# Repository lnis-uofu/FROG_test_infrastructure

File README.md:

OpenFPGA-FROG_12nm-Infrastructure is the repository containing all the informations regarding LNIS's FROG12nm based boards.
Here is a description of this repository content, more detailled Readmes to be found inside each directory.

# Pre-requisites

Operating system:

There is no operating system hard requirement, however development has been done under <complete OS> hence we recommend using this one especially when working on the firmware.

Development tools:

- Eagle 9.6.2 - Download [HERE](http://eagle.autodesk.com/eagle/software-versions/50)
- AutoCAD 2022 (optional, Drawing tool for wirebonding schematics)  - Download [HERE](https://www.autodesk.com/products/autocad/free-trial)
- Vivado 2020 - Download [HERE](https://www.xilinx.com/support/download/index.html/content/xilinx/en/downloadNav/vivado-design-tools/2020-3.html)

# Directory description

 - ./Packaging: Package manufacturing & assembly files with documentation. We employed the Open Source BaseJump UCSD_BGA_332 from the Bespoke Silicon Group (https://bsg.ai).
 - ./Testboard: Contains design files for every board / component related to the POSHtestbed project. Also contains testfirmware that has been used to test FROG chip.
 - ./Demoboard: Design files for the 3 demoboard versions.

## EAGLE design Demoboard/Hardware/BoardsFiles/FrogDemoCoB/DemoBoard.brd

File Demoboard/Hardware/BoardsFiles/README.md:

#BoardsFiles Folder Structure

TODO: Describe the 3 boards and what's inside the folders

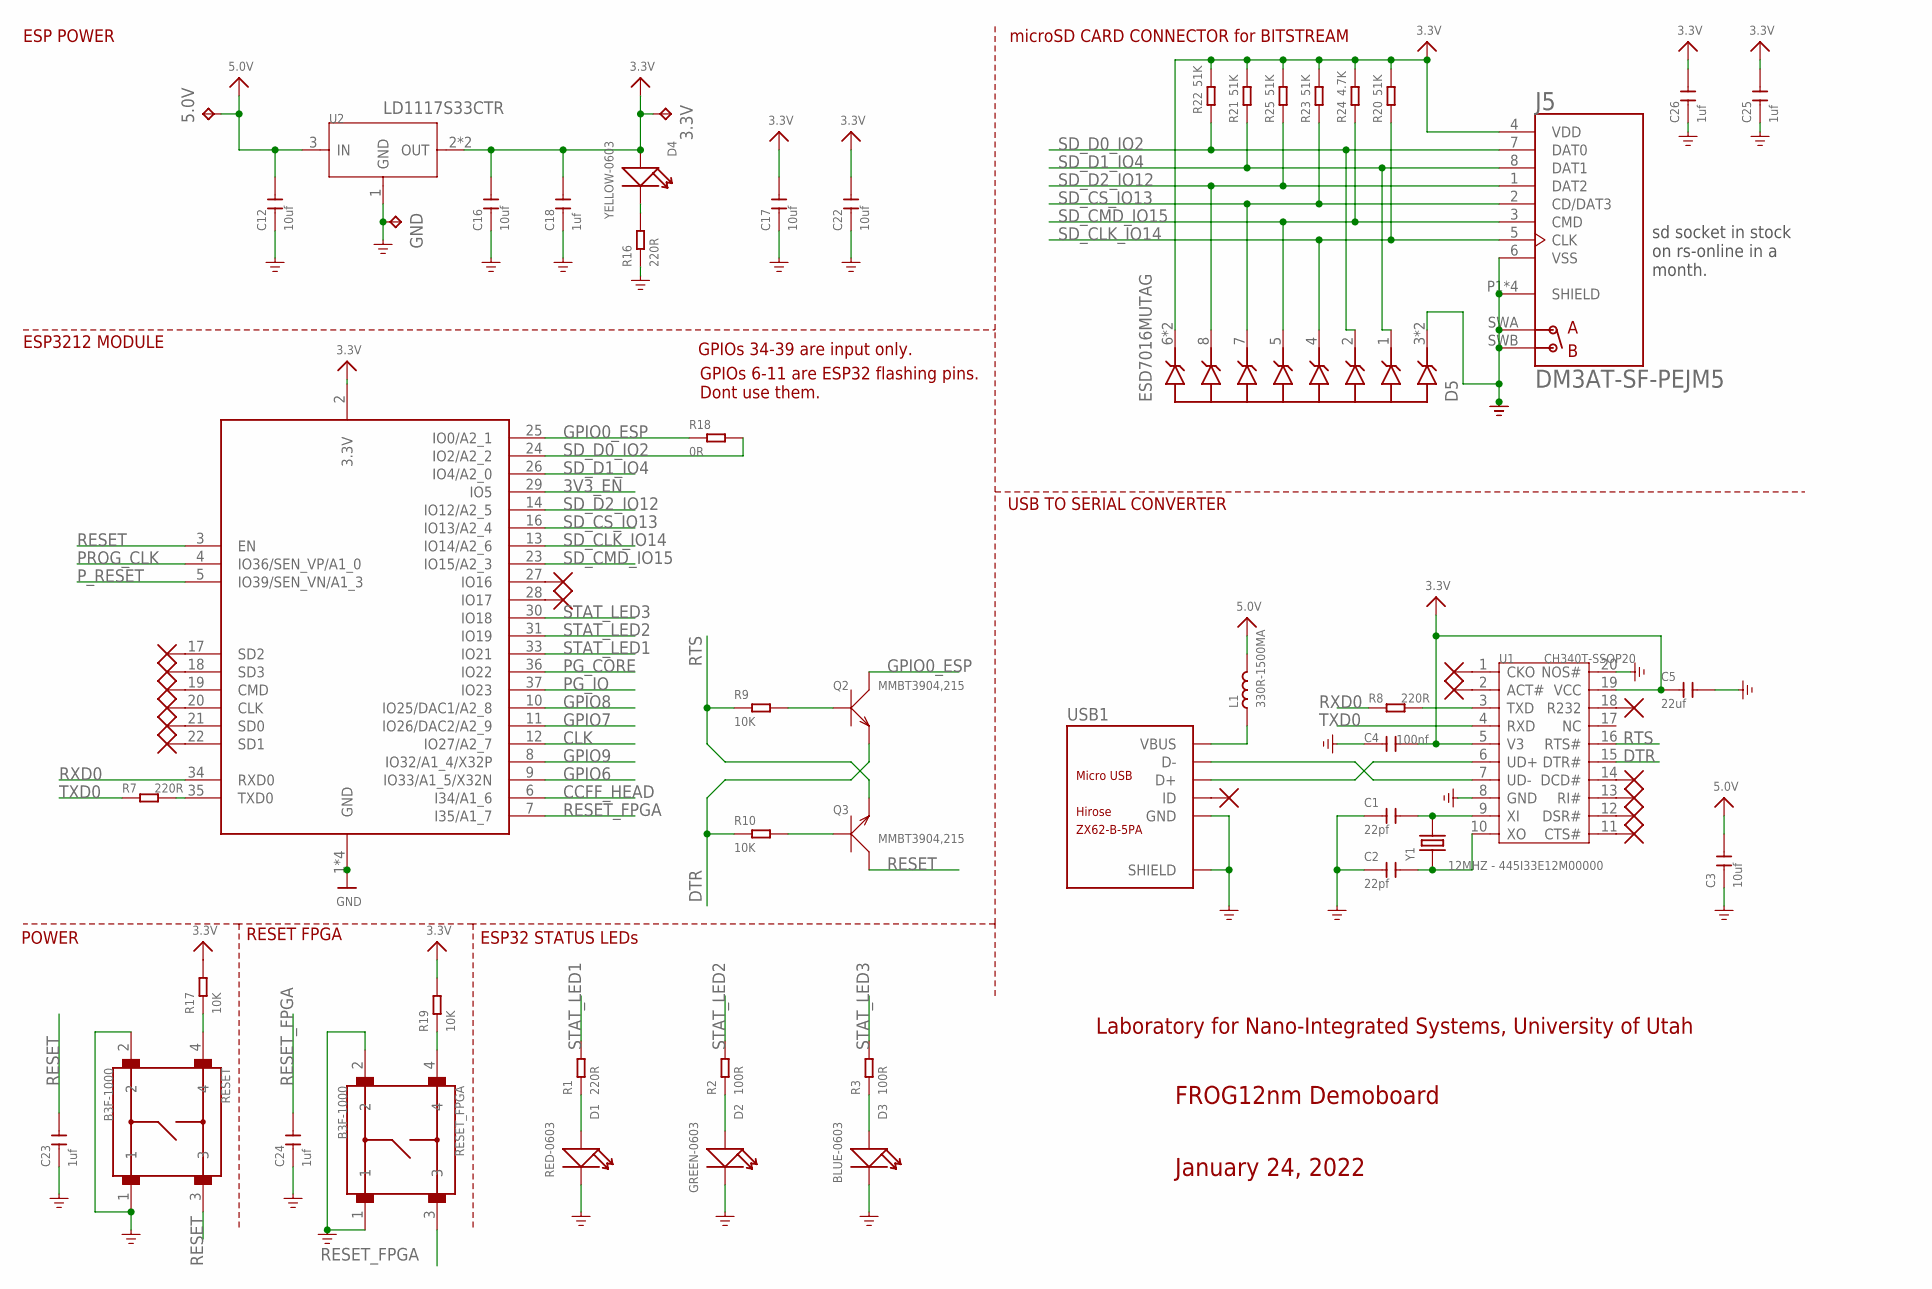
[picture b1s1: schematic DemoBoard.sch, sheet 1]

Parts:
3.3V, 5.0V: TPTP20SQ; TP20SQ
C1, C2: 22pf; C0603
C3, C12, C16, C17, C22: 10uf; C0603
C4: 100nf; C0603
C5: 22uf; C0805
C18, C23, C24, C25, C26: 1uf; C0603
D1: RED-0603; LED-0603
D2: GREEN-0603; LED-0603
D3: BLUE-0603; LED-0603
D4: YELLOW-0603; LED-0603
D5: ESD7016MUTAG; TVS_ESD7016MUTAG
GND: TPTP20SQ; TP20SQ
J5: DM3AT-SF-PEJM5; HRS_DM3AT-SF-PEJM5
L1: 330R-1500MA; L0805
Q2, Q3: MMBT3904,215; SOT-23
R1, R7, R8, R16: 220R; R0603
R2, R3: 100R; R0603
R9, R10, R17, R19: 10K; R0603
R18: 0R; R0603
R20, R21, R22, R23, R25: 51K; R0603
R24: 4.7K; R0603
RESET: B3F-1000; SW_B3F-1000
RESET_FPGA: B3F-1000; SW_B3F-1000
U1: CH340T-SSOP20; SSOP20-0.65-7.6X5.2MM
U2: PMIC-CJT1117-3.3(SOT223); SOT-223; MPN LD1117S33CTR
U3: ESP32_WROOM32_SKINNY; WROOM32_SKINNY
USB1: ZX62-B-5PA; MICRO-USB5+6P-SMD-0.65-AB
Y1: 12MHZ - 445I33E12M00000; X2-SMD-5.0X3.2X1.3MM

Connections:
3.3V: 3.3V.TP, C4.2, C5.1, C16.2, C17.2, C18.2, C22.2, C25.2, C26.2, D4.+, D5.6 (GND), D5.9 (GND), J5.4 (VDD), R17.2, R19.2, R20.2, R21.2, R22.2, R23.2, R24.2, R25.2, U1.5 (V3), U1.19 (VCC), U2.2 (OUT), U2.TER (OUT), U3.2 (3.3V); also elsewhere on the board
3V3_EN: U3.29 (IO5); also elsewhere on the board
5.0V: 5.0V.TP, C3.2, C12.2, L1.2, U2.3 (IN); also elsewhere on the board
CCFF_HEAD: U3.6 (I34/A1_6); also elsewhere on the board
CLK: U3.12 (IO27/A2_7); also elsewhere on the board
DTR: Q2.2 (E), R10.1, U1.15 (DTR#)
GND: C1.1, C2.1, C3.1, C4.1, C5.2, C12.1, C16.1, C17.1, C18.1, C22.1, C23.1, C24.1, C25.1, C26.1, D1.-, D2.-, D3.-, D5.3 (VBUS), D5.10 (VBUS), GND.TP, J5.6 (VSS), J5.P1 (SHIELD), J5.P2 (SHIELD), J5.P3 (SHIELD), J5.P4 (SHIELD), J5.SWA (A), J5.SWB (B), R16.1, RESET.1, RESET.2, RESET_FPGA.1, RESET_FPGA.2, U1.8 (GND), U1.20 (NOS#), U2.1 (GND), U3.1 (GND), U3.15 (GND), U3.38 (GND), U3.P$1 (GND), USB1.5 (GND), USB1.P1 (SHIELD), USB1.P2 (SHIELD), USB1.P3_1 (SHIELD), USB1.P3_2 (SHIELD), USB1.P3_3 (SHIELD), USB1.P4_1 (SHIELD), USB1.P4_2 (SHIELD), USB1.P4_3 (SHIELD), USB1.P5 (SHIELD), USB1.P6 (SHIELD); also elsewhere on the board
GPIO0_ESP: Q2.3 (C), R18.1, U3.25 (IO0/A2_1)
GPIO6: U3.9 (IO33/A1_5/X32N); also elsewhere on the board
GPIO7: U3.11 (IO26/DAC2/A2_9); also elsewhere on the board
GPIO8: U3.10 (IO25/DAC1/A2_8); also elsewhere on the board
GPIO9: U3.8 (IO32/A1_4/X32P); also elsewhere on the board
unnamed: D2.+, R2.1
unnamed: R17.1, RESET.4
unnamed: R19.1, RESET_FPGA.4
unnamed: D1.+, R1.1
unnamed: Q3.1 (B), R10.2
unnamed: Q2.1 (B), R9.2
unnamed: D3.+, R3.1
unnamed: D4.-, R16.2
unnamed: U1.7 (UD-), USB1.2 (D-)
unnamed: U1.6 (UD+), USB1.3 (D+)
unnamed: C1.2, U1.9 (XI), Y1.2
unnamed: C2.2, U1.10 (XO), Y1.1
unnamed: R8.2, U1.3 (TXD)
unnamed: R7.2, U3.35 (TXD0)
PG_CORE: U3.36 (IO22); also elsewhere on the board
PG_IO: U3.37 (IO23); also elsewhere on the board
PROG_CLK: U3.4 (IO36/SEN_VP/A1_0); also elsewhere on the board
P_RESET: U3.5 (IO39/SEN_VN/A1_3); also elsewhere on the board
RESET: C23.2, Q3.3 (C), RESET.3, U3.3 (EN)
RESET_FPGA: C24.2, RESET_FPGA.3, U3.7 (I35/A1_7); also elsewhere on the board
RTS: Q3.2 (E), R9.1, U1.16 (RTS#)
RXD0: R8.1, U3.34 (RXD0)
SD_CLK_IO14: D5.4 (I/O3), J5.5 (CLK), R20.1, U3.13 (IO14/A2_6)
SD_CMD_IO15: D5.5 (I/O4), J5.3 (CMD), R24.1, U3.23 (IO15/A2_3)
SD_CS_IO13: D5.7 (I/O5), J5.2 (CD/DAT3), R23.1, U3.16 (IO13/A2_4)
SD_D0_IO2: D5.2 (I/O2), J5.7 (DAT0), R18.2, R22.1, U3.24 (IO2/A2_2)
SD_D1_IO4: D5.1 (I/O1), J5.8 (DAT1), R21.1, U3.26 (IO4/A2_0)
SD_D2_IO12: D5.8 (I/O6), J5.1 (DAT2), R25.1, U3.14 (IO12/A2_5)
STAT_LED1: R1.2, U3.33 (IO21)
STAT_LED2: R2.2, U3.31 (IO19)
STAT_LED3: R3.2, U3.30 (IO18)
TXD0: R7.1, U1.4 (RXD)
VBUS: L1.1, USB1.1 (VBUS)

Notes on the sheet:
ESP POWER
RESET FPGA
USB TO SERIAL CONVERTER
ESP3212 MODULE
POWER
microSD CARD CONNECTOR for BITSTREAM
FROG12nm Demoboard
January 24, 2022
ESP32 STATUS LEDs
GPIOs 34-39 are input only.
Laboratory for Nano-Integrated Systems, University of Utah
GPIOs 6-11 are ESP32 flashing pins. Dont use them.
sd socket in stock on rs-online in a month.

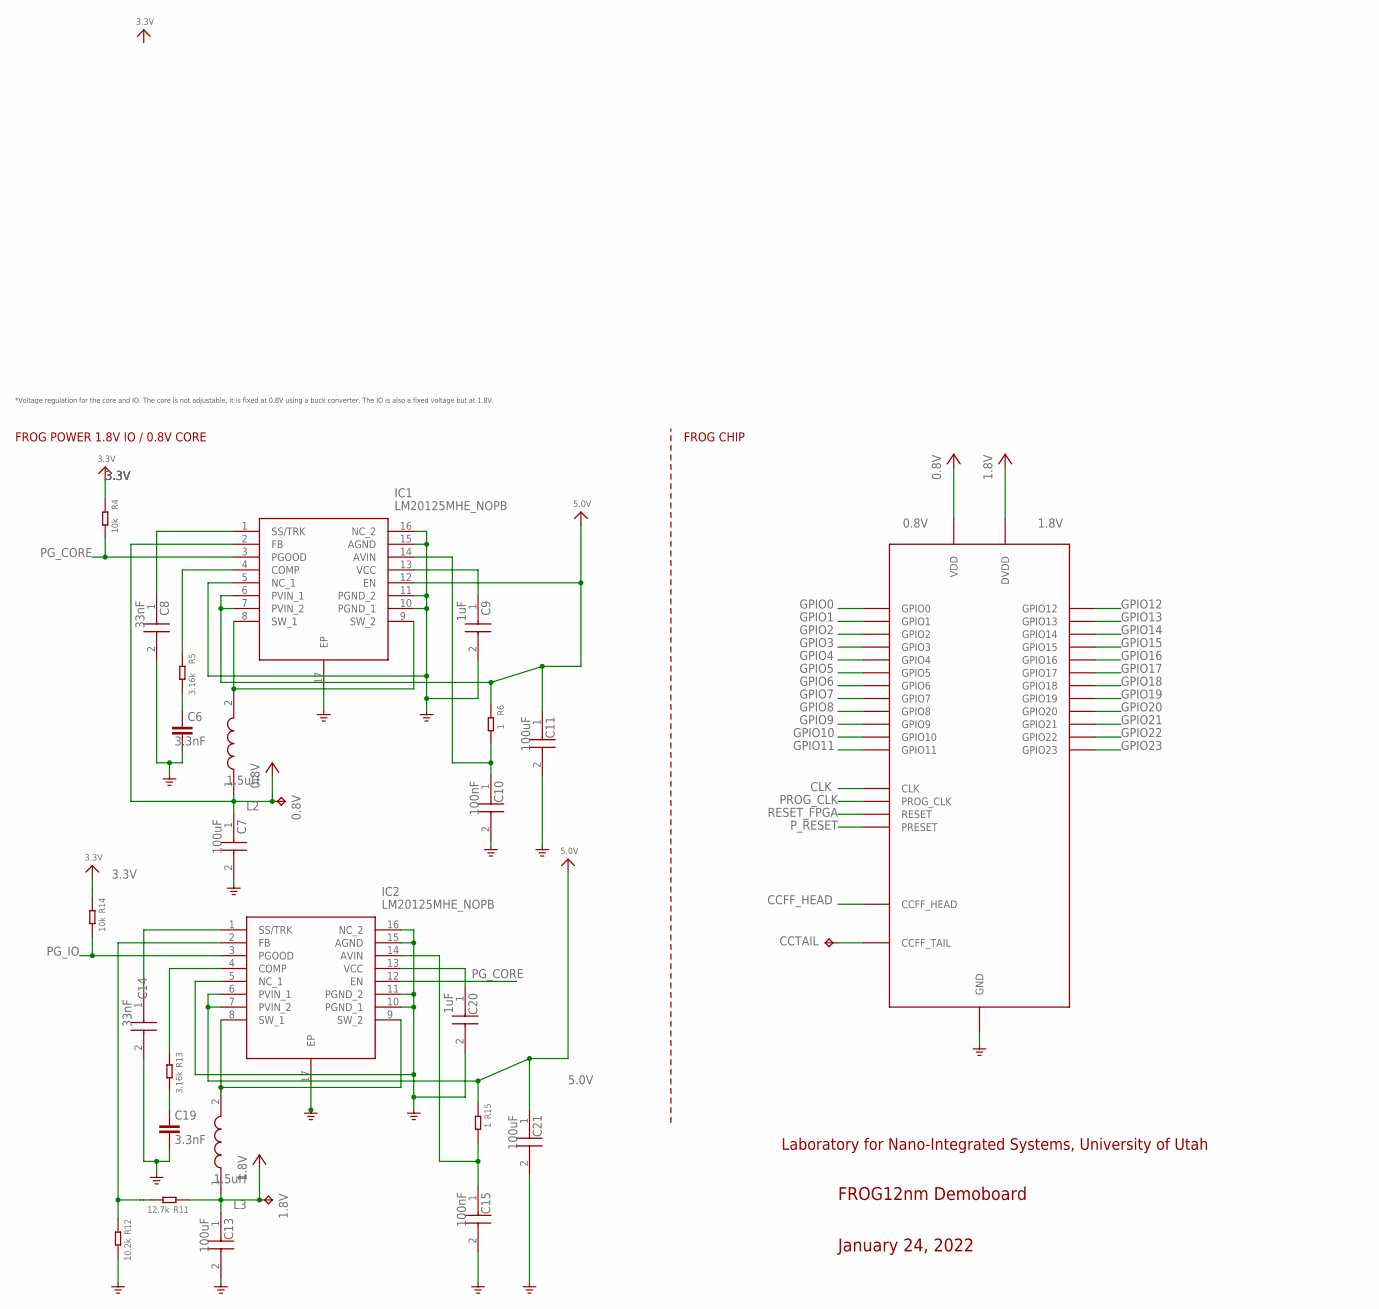
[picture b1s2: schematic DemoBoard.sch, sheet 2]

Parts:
0.8V, 1.8V: TPTP20SQ; TP20SQ
C6, C19: 3.3nF; CAPC1608X85
C7, C11, C13, C21: 100uF; CAPC3225X270N
C8, C14: 33nF; CAPC1608X97N
C9, C20: 1uF; CAPC1005X55N
C10, C15: 100nF; CAPC1005X55N
CCTAIL: TPPAD1-13; P1-13
IC1, IC2: LM20125MHE_NOPB; SOP65P640X120-17N
L2, L3: 1.5uH; INDPM7066X300N
R4, R14: 10k; R0603
R5, R13: 3.16k; R0603
R6, R15: 1; R0603
R11: 12.7k; R0603
R12: 10.2k; R0603
U5: FROG12NMCOBCOB; FROG_COB

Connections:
0.8V: 0.8V.TP, C7.1, IC1.2 (FB), L2.1, U5.VDD_CORE (VDD)
1.8V: 1.8V.TP, C13.1, L3.1, R11.1, U5.VDD_IO (DVDD)
3.3V: R4.1, R14.1; also elsewhere on the board
5.0V: C11.1, C21.1, IC1.6 (PVIN_1), IC1.7 (PVIN_2), IC1.12 (EN), IC2.6 (PVIN_1), IC2.7 (PVIN_2), R6.1, R15.1; also elsewhere on the board
CCFF_HEAD: U5.CCFFHEAD (CCFF_HEAD); also elsewhere on the board
CLK: U5.CLK; also elsewhere on the board
GND: C6.2, C7.2, C8.2, C9.2, C10.2, C11.2, C13.2, C14.2, C15.2, C19.2, C20.2, C21.2, IC1.5 (NC_1), IC1.10 (PGND_1), IC1.11 (PGND_2), IC1.15 (AGND), IC1.16 (NC_2), IC1.17 (EP), IC2.5 (NC_1), IC2.10 (PGND_1), IC2.11 (PGND_2), IC2.15 (AGND), IC2.16 (NC_2), IC2.17 (EP), R12.2, U5.GND; also elsewhere on the board
GPIO0: U5.GPIO0; also elsewhere on the board
GPIO1: U5.GPIO1; also elsewhere on the board
GPIO2: U5.GPIO2; also elsewhere on the board
GPIO3: U5.GPIO3; also elsewhere on the board
GPIO4: U5.GPIO4; also elsewhere on the board
GPIO5: U5.GPIO5; also elsewhere on the board
GPIO6: U5.GPIO6; also elsewhere on the board
GPIO7: U5.GPIO7; also elsewhere on the board
GPIO8: U5.GPIO8; also elsewhere on the board
GPIO9: U5.GPIO9; also elsewhere on the board
GPIO10: U5.GPIO10; also elsewhere on the board
GPIO11: U5.GPIO11; also elsewhere on the board
GPIO12: U5.GPIO12; also elsewhere on the board
GPIO13: U5.GPIO13; also elsewhere on the board
GPIO14: U5.GPIO14; also elsewhere on the board
GPIO15: U5.GPIO15; also elsewhere on the board
GPIO16: U5.GPIO16; also elsewhere on the board
GPIO17: U5.GPIO17; also elsewhere on the board
GPIO18: U5.GPIO18; also elsewhere on the board
GPIO19: U5.GPIO19; also elsewhere on the board
GPIO20: U5.GPIO20; also elsewhere on the board
GPIO21: U5.GPIO21; also elsewhere on the board
GPIO22: U5.GPIO22; also elsewhere on the board
GPIO23: U5.GPIO23; also elsewhere on the board
unnamed: IC1.4 (COMP), R5.1
unnamed: C6.1, R5.2
unnamed: C9.1, IC1.13 (VCC)
unnamed: C8.1, IC1.1 (SS/TRK)
unnamed: IC1.8 (SW_1), IC1.9 (SW_2), L2.2
unnamed: CCTAIL.TP, U5.CCFFTAIL (CCFF_TAIL)
unnamed: C10.1, IC1.14 (AVIN), R6.2
unnamed: IC2.4 (COMP), R13.1
unnamed: C19.1, R13.2
unnamed: C20.1, IC2.13 (VCC)
unnamed: C14.1, IC2.1 (SS/TRK)
unnamed: IC2.8 (SW_1), IC2.9 (SW_2), L3.2
unnamed: C15.1, IC2.14 (AVIN), R15.2
PG_CORE: IC1.3 (PGOOD), IC2.12 (EN), R4.2; also elsewhere on the board
PG_IO: IC2.3 (PGOOD), R14.2; also elsewhere on the board
PROG_CLK: U5.PROGCLK (PROG_CLK); also elsewhere on the board
P_RESET: U5.PRESET; also elsewhere on the board
RESET_FPGA: U5.RESET; also elsewhere on the board
VDD_CORE: IC2.2 (FB), R11.2, R12.1

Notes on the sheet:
FROG12nm Demoboard
January 24, 2022
Laboratory for Nano-Integrated Systems, University of Utah
*Voltage regulation for the core and IO. The core is not adjustable, it is fixed at 0.8V using a buck converter. The IO is also a fixed voltage but at 1.8V.
FROG POWER 1.8V IO / 0.8V CORE
FROG CHIP

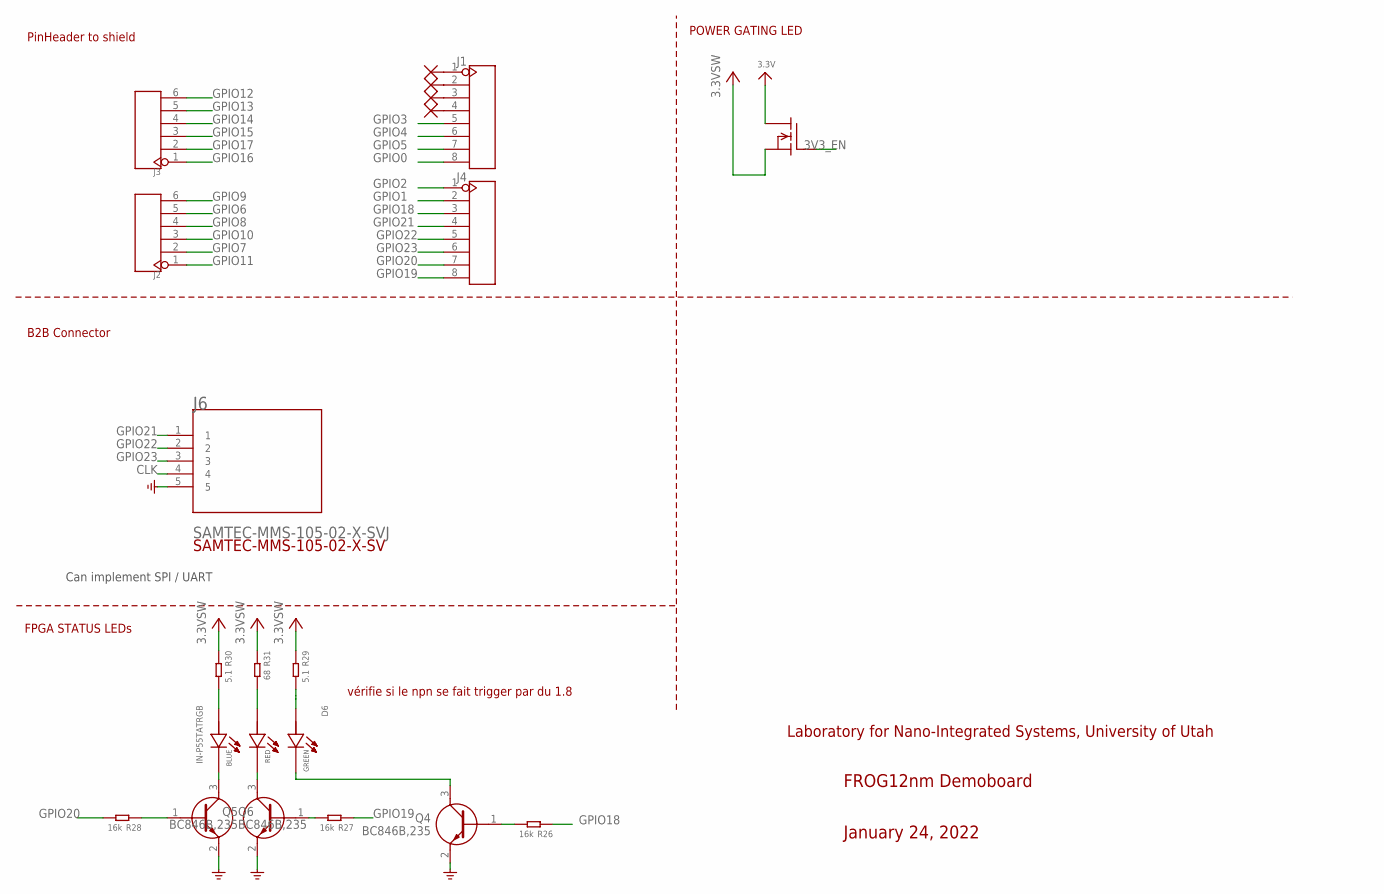
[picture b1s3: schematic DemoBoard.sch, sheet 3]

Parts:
D6: IN-P55TATRGB; LED_IN-P55TATRGB
J1, J4: HEADER-8P-2.54; 8P-2.54
J2, J3: HEADER-6P-55/35MIL; 6P-2.54-55/35MIL
J6: SAMTEC-MMS-105-02-X-SVJ; SAMTEC-MMS-105-02-X-SV
Q1: IRLML0030TRPBF; SOT23
Q4, Q5, Q6: BC846B,235; SOT95P230X110-3N
R26, R27, R28: 16k; R0603
R29, R30: 5.1; R0603
R31: 68; R0603

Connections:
3.3V: Q1.3 (D); also elsewhere on the board
3.3VSW: Q1.2 (S), R29.1, R30.1, R31.1
3V3_EN: Q1.1 (G); also elsewhere on the board
CLK: J6.4; also elsewhere on the board
GND: J6.5, Q4.2 (E), Q5.2 (E), Q6.2 (E); also elsewhere on the board
GPIO0: J1.8; also elsewhere on the board
GPIO1: J4.2; also elsewhere on the board
GPIO2: J4.1; also elsewhere on the board
GPIO3: J1.5; also elsewhere on the board
GPIO4: J1.6; also elsewhere on the board
GPIO5: J1.7; also elsewhere on the board
GPIO6: J2.5; also elsewhere on the board
GPIO7: J2.2; also elsewhere on the board
GPIO8: J2.4; also elsewhere on the board
GPIO9: J2.6; also elsewhere on the board
GPIO10: J2.3; also elsewhere on the board
GPIO11: J2.1; also elsewhere on the board
GPIO12: J3.6; also elsewhere on the board
GPIO13: J3.5; also elsewhere on the board
GPIO14: J3.4; also elsewhere on the board
GPIO15: J3.3; also elsewhere on the board
GPIO16: J3.1; also elsewhere on the board
GPIO17: J3.2; also elsewhere on the board
GPIO18: J4.3, R26.1; also elsewhere on the board
GPIO19: J4.8, R27.1; also elsewhere on the board
GPIO20: J4.7, R28.2; also elsewhere on the board
GPIO21: J4.4, J6.1; also elsewhere on the board
GPIO22: J4.5, J6.2; also elsewhere on the board
GPIO23: J4.6, J6.3; also elsewhere on the board
unnamed: D6.1 (B_C), Q6.3 (C)
unnamed: Q5.1 (B), R27.2
unnamed: D6.2 (R_C), Q5.3 (C)
unnamed: D6.3 (G_C), Q4.3 (C)
unnamed: Q6.1 (B), R28.1
unnamed: Q4.1 (B), R26.2
unnamed: D6.5 (R_A), R31.2
VCC2: D6.4 (G_A), D6.6 (B_A), R29.2, R30.2

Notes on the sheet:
FROG12nm Demoboard
January 24, 2022
Laboratory for Nano-Integrated Systems, University of Utah
B2B Connector
Can implement SPI / UART
PinHeader to shield
FPGA STATUS LEDs
vérifie si le npn se fait trigger par du 1.8
POWER GATING LED

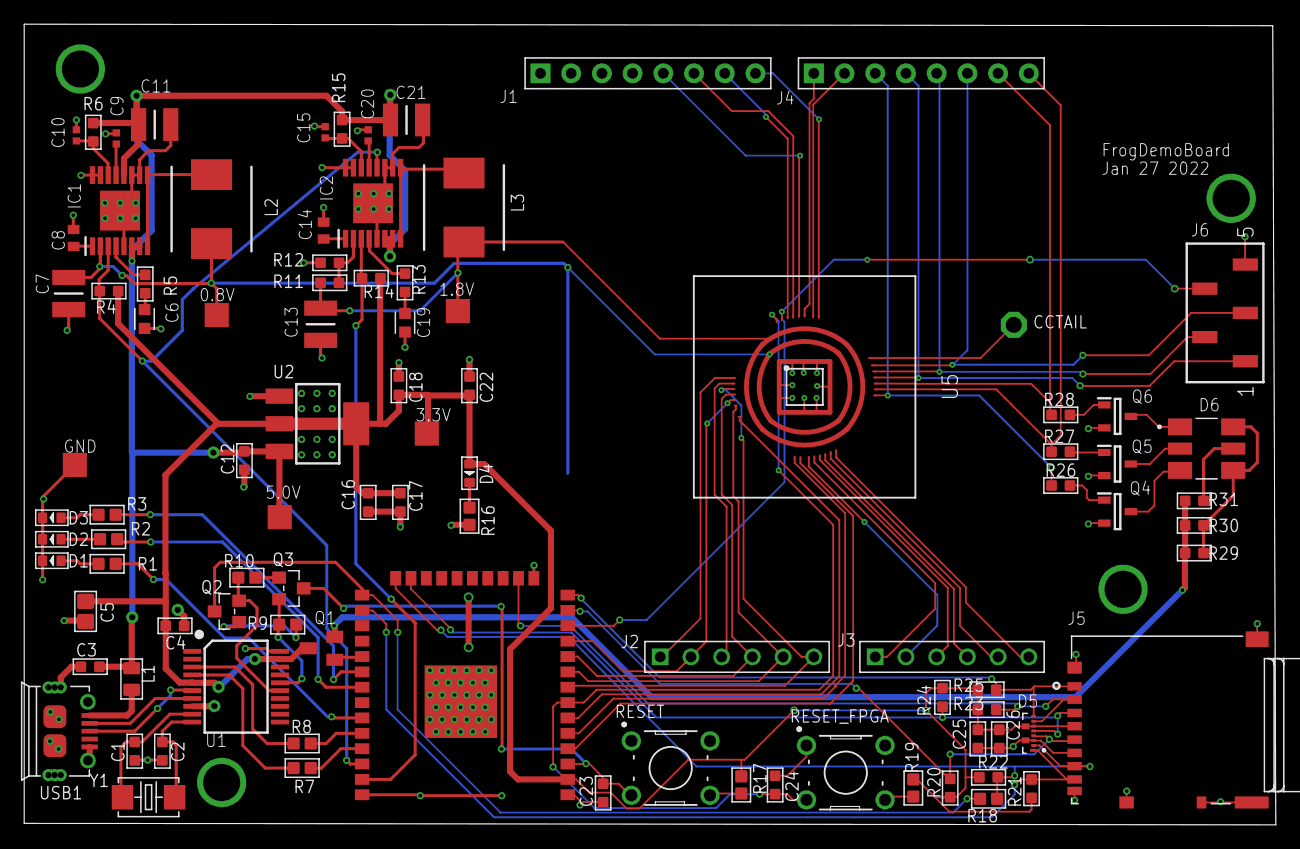
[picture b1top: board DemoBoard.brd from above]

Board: 2 copper layers, 103.5 x 66.2 mm, 94 parts (0 on the bottom side), 90 nets.

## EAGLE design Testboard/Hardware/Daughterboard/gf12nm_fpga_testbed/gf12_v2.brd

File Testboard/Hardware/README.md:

The testboard hardware folder contains design and documentation files for the POSH project test bed,
baseboard for the Trenz Electronic UltraSOM+ MPSoC (TE0803) and an additional custom daughter board (TEBF0808) to connect a VLSI circuit to be tested.

# Directory description

- ./AP-TEBF0808-04: Baseboard design files for the POSHtestbed project.
- ./Daughterboard: Custom board to connect FROG12_nm chip to the baseboard.
- ./ULTRASoMCarier: Carier card for above listed boards.
- ./Libraries: Common libraries for the project.
- ./Documentation: Boards documentation as well as critical components datasheets.
- ./TestSocket: TestSocket documentation that's being used to plug chips for testing.

# Trenz sources

UltraSOM MPSoC:
https://shop.trenz-electronic.de/en/TE0803-03-4BE11-A-MPSoC-Module-with-Xilinx-Zynq-UltraScale-ZU4EG-1E-2-GByte-DDR4-5.2-x-7.6-cm

Carrier Card:
https://shop.trenz-electronic.de/en/TEBF0808-04A-UltraITX-Baseboard-for-Trenz-Electronic-TE080X-UltraSOM

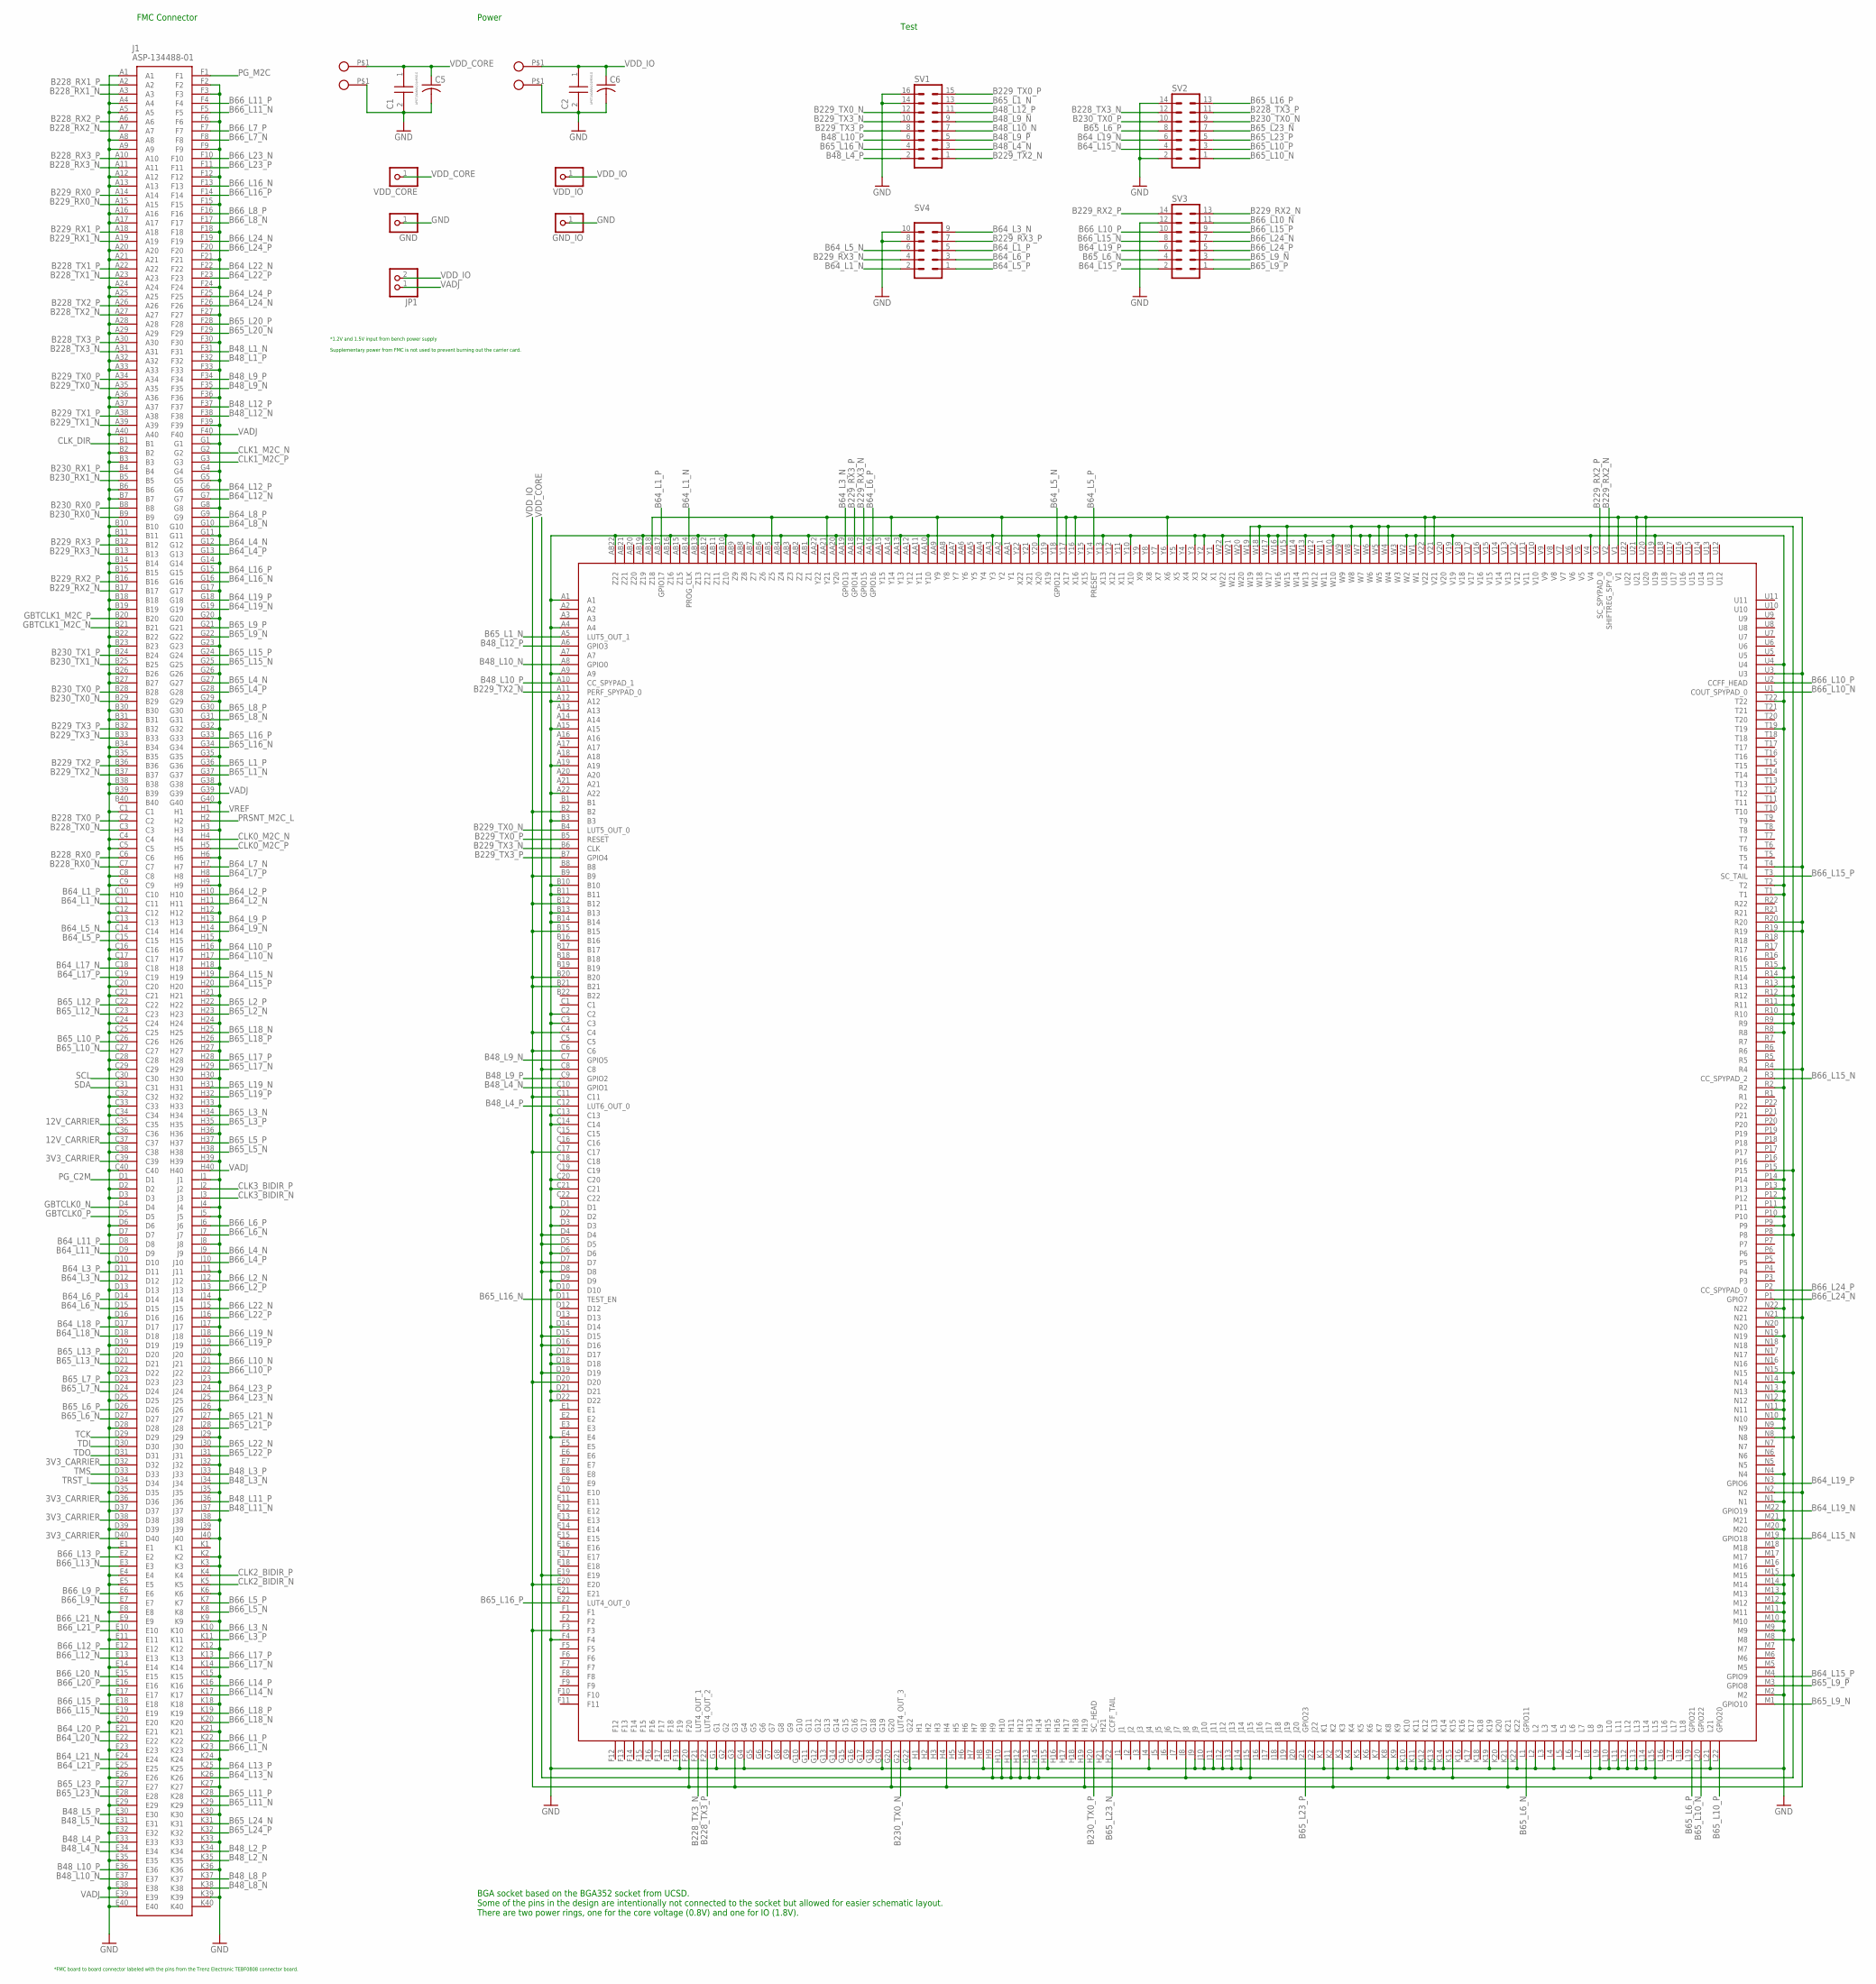
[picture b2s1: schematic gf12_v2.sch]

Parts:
C1, C2: APXT160ARA101ME61G; CAPAE530X610N
C5, C6: C-USC0805K; C0805K
GND: PINHD-1X1; 1X01
GND_IO: PINHD-1X1; 1X01
J1: ASP-134488-01; ASP13448801
JP1: PINHD-1X2; 1X02
SV1: MA08-2
SV2, SV3: MA07-2
SV4: MA05-2
U$2: BGA352; BGA484C100P22X22_2400X2400X220N
U$3, U$4, U$5: BANANA_JACK; 73099
VDD: BANANA_JACK; 73099
VDD_CORE: PINHD-1X1; 1X01
VDD_IO: PINHD-1X1; 1X01

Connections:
3V3_CARRIER: J1.C39, J1.D32, J1.D36, J1.D38, J1.D40
12V_CARRIER: J1.C35, J1.C37
B48_L1_N: J1.F31
B48_L1_P: J1.F32
B48_L2_N: J1.K35
B48_L2_P: J1.K34
B48_L3_N: J1.J34
B48_L3_P: J1.J33
B48_L4_N: J1.E34, SV1.3, U$2.C10 (GPIO1)
B48_L4_P: J1.E33, SV1.2, U$2.C12 (LUT6_OUT_0)
B48_L5_N: J1.E31
B48_L5_P: J1.E30
B48_L8_N: J1.K38
B48_L8_P: J1.K37
B48_L9_N: J1.F35, SV1.9, U$2.C7 (GPIO5)
B48_L9_P: J1.F34, SV1.5, U$2.C9 (GPIO2)
B48_L10_N: J1.E37, SV1.7, U$2.A8 (GPIO0)
B48_L10_P: J1.E36, SV1.6, U$2.A10 (CC_SPYPAD_1)
B48_L11_N: J1.J37
B48_L11_P: J1.J36
B48_L12_N: J1.F38
B48_L12_P: J1.F37, SV1.11, U$2.A6 (GPIO3)
B64_L1_N: J1.C11, SV4.2, U$2.AB14 (PROG_CLK)
B64_L1_P: J1.C10, SV4.5, U$2.AB17 (GPIO17)
B64_L2_N: J1.H11
B64_L2_P: J1.H10
B64_L3_N: J1.D12, SV4.9, U$2.AA19 (GPIO13)
B64_L3_P: J1.D11
B64_L4_N: J1.G12
B64_L4_P: J1.G13
B64_L5_N: J1.C14, SV4.6, U$2.Y18 (GPIO12)
B64_L5_P: J1.C15, SV4.1, U$2.Y14 (PRESET)
B64_L6_N: J1.D15
B64_L6_P: J1.D14, SV4.3, U$2.AA16 (GPIO16)
B64_L7_N: J1.H7
B64_L7_P: J1.H8
B64_L8_N: J1.G10
B64_L8_P: J1.G9
B64_L9_N: J1.H14
B64_L9_P: J1.H13
B64_L10_N: J1.H17
B64_L10_P: J1.H16
B64_L11_N: J1.D9
B64_L11_P: J1.D8
B64_L12_N: J1.G7
B64_L12_P: J1.G6
B64_L13_N: J1.K26
B64_L13_P: J1.K25
B64_L15_N: J1.H19, SV2.4, U$2.M19 (GPIO18)
B64_L15_P: J1.H20, SV3.2, U$2.M4 (GPIO9)
B64_L16_N: J1.G16
B64_L16_P: J1.G15
B64_L17_N: J1.C18
B64_L17_P: J1.C19
B64_L18_N: J1.D18
B64_L18_P: J1.D17
B64_L19_N: J1.G19, SV2.6, U$2.M22 (GPIO19)
B64_L19_P: J1.G18, SV3.6, U$2.N3 (GPIO6)
B64_L20_N: J1.E22
B64_L20_P: J1.E21
B64_L21_N: J1.E24
B64_L21_P: J1.E25
B64_L22_N: J1.F22
B64_L22_P: J1.F23
B64_L23_N: J1.J25
B64_L23_P: J1.J24
B64_L24_N: J1.F26
B64_L24_P: J1.F25
B65_L1_N: J1.G37, SV1.13, U$2.A5 (LUT5_OUT_1)
B65_L1_P: J1.G36
B65_L2_N: J1.H23
B65_L2_P: J1.H22
B65_L3_N: J1.H34
B65_L3_P: J1.H35
B65_L4_N: J1.G27
B65_L4_P: J1.G28
B65_L5_N: J1.H38
B65_L5_P: J1.H37
B65_L6_N: J1.D27, SV3.4, U$2.L1 (GPIO11)
B65_L6_P: J1.D26, SV2.8, U$2.L19 (GPIO21)
B65_L7_N: J1.D24
B65_L7_P: J1.D23
B65_L8_N: J1.G31
B65_L8_P: J1.G30
B65_L9_N: J1.G22, SV3.3, U$2.M1 (GPIO10)
B65_L9_P: J1.G21, SV3.1, U$2.M3 (GPIO8)
B65_L10_N: J1.C27, SV2.1, U$2.L20 (GPIO22)
B65_L10_P: J1.C26, SV2.3, U$2.L22 (GPIO20)
B65_L11_N: J1.K29
B65_L11_P: J1.K28
B65_L12_N: J1.C23
B65_L12_P: J1.C22
B65_L13_N: J1.D21
B65_L13_P: J1.D20
B65_L15_N: J1.G25
B65_L15_P: J1.G24
B65_L16_N: J1.G34, SV1.4, U$2.D11 (TEST_EN)
B65_L16_P: J1.G33, SV2.13, U$2.E22 (LUT4_OUT_0)
B65_L17_N: J1.H29
B65_L17_P: J1.H28
B65_L18_N: J1.H25
B65_L18_P: J1.H26
B65_L19_N: J1.H31
B65_L19_P: J1.H32
B65_L20_N: J1.F29
B65_L20_P: J1.F28
B65_L21_N: J1.J27
B65_L21_P: J1.J28
B65_L22_N: J1.J30
B65_L22_P: J1.J31
B65_L23_N: J1.E28, SV2.7, U$2.H22 (CCFF_TAIL)
B65_L23_P: J1.E27, SV2.5, U$2.J21 (GPIO23)
B65_L24_N: J1.K31
B65_L24_P: J1.K32
B66_L1_N: J1.K23
B66_L1_P: J1.K22
B66_L2_N: J1.J12
B66_L2_P: J1.J13
B66_L3_N: J1.K10
B66_L3_P: J1.K11
B66_L4_N: J1.J9
B66_L4_P: J1.J10
B66_L5_N: J1.K8
B66_L5_P: J1.K7
B66_L6_N: J1.J7
B66_L6_P: J1.J6
B66_L7_N: J1.F8
B66_L7_P: J1.F7
B66_L8_N: J1.F17
B66_L8_P: J1.F16
B66_L9_N: J1.E7
B66_L9_P: J1.E6
B66_L10_N: J1.J21, SV3.11, U$2.U1 (COUT_SPYPAD_0)
B66_L10_P: J1.J22, SV3.10, U$2.U2 (CCFF_HEAD)
B66_L11_N: J1.F5
B66_L11_P: J1.F4
B66_L12_N: J1.E13
B66_L12_P: J1.E12
B66_L13_N: J1.E3
B66_L13_P: J1.E2
B66_L14_N: J1.K17
B66_L14_P: J1.K16
B66_L15_N: J1.E19, SV3.8, U$2.R3 (CC_SPYPAD_2)
B66_L15_P: J1.E18, SV3.9, U$2.T3 (SC_TAIL)
B66_L16_N: J1.F13
B66_L16_P: J1.F14
B66_L17_N: J1.K14
B66_L17_P: J1.K13
B66_L18_N: J1.K20
B66_L18_P: J1.K19
B66_L19_N: J1.J18
B66_L19_P: J1.J19
B66_L20_N: J1.E15
B66_L20_P: J1.E16
B66_L21_N: J1.E9
B66_L21_P: J1.E10
B66_L22_N: J1.J15
B66_L22_P: J1.J16
B66_L23_N: J1.F10
B66_L23_P: J1.F11
B66_L24_N: J1.F19, SV3.7, U$2.P1 (GPIO7)
B66_L24_P: J1.F20, SV3.5, U$2.P2 (CC_SPYPAD_0)
B228_RX0_N: J1.C7
B228_RX0_P: J1.C6
B228_RX1_N: J1.A3
B228_RX1_P: J1.A2
B228_RX2_N: J1.A7
B228_RX2_P: J1.A6
B228_RX3_N: J1.A11
B228_RX3_P: J1.A10
B228_TX0_N: J1.C3
B228_TX0_P: J1.C2
B228_TX1_N: J1.A23
B228_TX1_P: J1.A22
B228_TX2_N: J1.A27
B228_TX2_P: J1.A26
B228_TX3_N: J1.A31, SV2.12, U$2.F21 (LUT4_OUT_1)
B228_TX3_P: J1.A30, SV2.11, U$2.F22 (LUT4_OUT_2)
B229_RX0_N: J1.A15
B229_RX0_P: J1.A14
B229_RX1_N: J1.A19
B229_RX1_P: J1.A18
B229_RX2_N: J1.B17, SV3.13, U$2.V2 (SHIFTREG_SPY_0)
B229_RX2_P: J1.B16, SV3.14, U$2.V3 (SC_SPYPAD_0)
B229_RX3_N: J1.B13, SV4.4, U$2.AA17 (GPIO15)
B229_RX3_P: J1.B12, SV4.7, U$2.AA18 (GPIO14)
B229_TX0_N: J1.A35, SV1.12, U$2.B4 (LUT5_OUT_0)
B229_TX0_P: J1.A34, SV1.15, U$2.B5 (RESET)
B229_TX1_N: J1.A39
B229_TX1_P: J1.A38
B229_TX2_N: J1.B37, SV1.1, U$2.A11 (PERF_SPYPAD_0)
B229_TX2_P: J1.B36
B229_TX3_N: J1.B33, SV1.10, U$2.B6 (CLK)
B229_TX3_P: J1.B32, SV1.8, U$2.B7 (GPIO4)
B230_RX0_N: J1.B9
B230_RX0_P: J1.B8
B230_RX1_N: J1.B5
B230_RX1_P: J1.B4
B230_TX0_N: J1.B29, SV2.9, U$2.G21 (LUT4_OUT_3)
B230_TX0_P: J1.B28, SV2.10, U$2.H20 (SC_HEAD)
B230_TX1_N: J1.B25
B230_TX1_P: J1.B24
CLK0_M2C_N: J1.H4
CLK0_M2C_P: J1.H5
CLK1_M2C_N: J1.G2
CLK1_M2C_P: J1.G3
CLK2_BIDIR_N: J1.K5
CLK2_BIDIR_P: J1.K4
CLK3_BIDIR_N: J1.J3
CLK3_BIDIR_P: J1.J2
CLK_DIR: J1.B1
GBTCLK0_N: J1.D4
GBTCLK0_P: J1.D5
GBTCLK1_M2C_N: J1.B21
GBTCLK1_M2C_P: J1.B20
GND: C1.2 (-), C2.2 (-), C5.2, C6.2, GND.1, GND_IO.1, J1.A1, J1.A4, J1.A5, J1.A8, J1.A9, J1.A12, J1.A13, J1.A16, J1.A17, J1.A20, J1.A21, J1.A24, J1.A25, J1.A28, J1.A29, J1.A32, J1.A33, J1.A36, J1.A37, J1.A40, J1.B2, J1.B3, J1.B6, J1.B7, J1.B10, J1.B11, J1.B14, J1.B15, J1.B18, J1.B19, J1.B22, J1.B23, J1.B26, J1.B27, J1.B30, J1.B31, J1.B34, J1.B35, J1.B38, J1.B39, J1.C1, J1.C4, J1.C5, J1.C8, J1.C9, J1.C12, J1.C13, J1.C16, J1.C17, J1.C20, J1.C21, J1.C24, J1.C25, J1.C28, J1.C29, J1.C32, J1.C33, J1.C34, J1.C36, J1.C38, J1.C40, J1.D2, J1.D3, J1.D6, J1.D7, J1.D10, J1.D13, J1.D16, J1.D19, J1.D22, J1.D25, J1.D28, J1.D35, J1.D37, J1.D39, J1.E1, J1.E4, J1.E5, J1.E8, J1.E11, J1.E14, J1.E17, J1.E20, J1.E23, J1.E26, J1.E29, J1.E32, J1.E35, J1.E38, J1.E40, J1.F2, J1.F3, J1.F6, J1.F9, J1.F12, J1.F15, J1.F18, J1.F21, J1.F24, J1.F27, J1.F30, J1.F33, J1.F36, J1.F39, J1.G1, J1.G4, J1.G5, J1.G8, J1.G11, J1.G14, J1.G17, J1.G20, J1.G23, J1.G26, J1.G29, J1.G32, J1.G35, J1.G38, J1.G40, J1.H3, J1.H6, J1.H9, J1.H12, J1.H15, J1.H18, J1.H21, J1.H24, J1.H27, J1.H30, J1.H33, J1.H36, J1.H39, J1.J1, J1.J4, J1.J5, J1.J8, J1.J11, J1.J14, J1.J17, J1.J20, J1.J23, J1.J26, J1.J29, J1.J32, J1.J35, J1.J38, J1.J40, J1.K2, J1.K3, J1.K6, J1.K9, J1.K12, J1.K15, J1.K18, J1.K21, J1.K24, J1.K27, J1.K30, J1.K33, J1.K36, J1.K39, SV1.14, SV1.16, SV2.2, SV2.14, SV3.12, SV4.8, SV4.10, U$2.A1, U$2.A4, U$2.A9, U$2.A12, U$2.A15, U$2.A19, U$2.A22, U$2.AA3 (Y3), U$2.AA10 (Y10), U$2.AA13 (Y13), U$2.AA20 (Y20), U$2.AB1 (Z1), U$2.AB4 (Z4), U$2.AB7 (Z7), U$2.AB10 (Z10), U$2.AB13 (Z13), U$2.AB16 (Z16), U$2.AB19 (Z19), U$2.AB22 (Z22), U$2.B3, U$2.B10, U$2.B11, U$2.B13, U$2.B14, U$2.C2, U$2.C3, U$2.C13, U$2.C14, U$2.C20, U$2.C21, U$2.D1, U$2.D3, U$2.D6, U$2.D9, U$2.D10, U$2.D14, U$2.D17, U$2.D18, U$2.D21, U$2.D22, U$2.E4, U$2.F4, U$2.F19, U$2.G1, U$2.G4, U$2.G19, U$2.G22, U$2.H8, U$2.H15, U$2.J4, U$2.J9, U$2.J10, U$2.J11, U$2.J12, U$2.J13, U$2.J14, U$2.K1, U$2.K4, U$2.K9, U$2.K10, U$2.K11, U$2.K12, U$2.K13, U$2.K14, U$2.K19, U$2.K22, U$2.L2, U$2.L4, U$2.L9, U$2.L10, U$2.L11, U$2.L12, U$2.L13, U$2.L14, U$2.L21, U$2.M2, U$2.M9, U$2.M10, U$2.M11, U$2.M12, U$2.M13, U$2.M14, U$2.M20, U$2.M21, U$2.N1, U$2.N4, U$2.N9, U$2.N10, U$2.N11, U$2.N12, U$2.N13, U$2.N14, U$2.N19, U$2.N22, U$2.P9, U$2.P10, U$2.P11, U$2.P12, U$2.P13, U$2.P14, U$2.R2, U$2.R8, U$2.R15, U$2.T1, U$2.T2, U$2.T19, U$2.T22, U$2.U4, U$2.U19, U$2.V4, U$2.V19, U$2.W1, U$2.W2, U$2.W6, U$2.W7, U$2.W10, U$2.W13, U$2.W16, U$2.W17, U$2.W22, U$2.Y2 (X2), U$2.Y3 (X3), U$2.Y10 (X10), U$2.Y13 (X13), U$2.Y20 (X20), U$3.P$1 (1), U$3.P$2 (GND), U$3.P$3 (GND), U$3.P$4 (GND), U$3.P$5 (GND), U$4.P$2 (GND), U$4.P$3 (GND), U$4.P$4 (GND), U$4.P$5 (GND), U$5.P$1 (1), U$5.P$2 (GND), U$5.P$3 (GND), U$5.P$4 (GND), U$5.P$5 (GND), VDD.P$2 (GND), VDD.P$3 (GND), VDD.P$4 (GND), VDD.P$5 (GND)
PG_C2M: J1.D1
PG_M2C: J1.F1
PRSNT_M2C_L: J1.H2
SCL: J1.C30
SDA: J1.C31
TCK: J1.D29
TDI: J1.D30
TDO: J1.D31
TMS: J1.D33
TRST_L: J1.D34
VADJ: J1.E39, J1.F40, J1.G39, J1.H40, JP1.1
VDD_CORE: C1.1 (+), C5.1, U$2.C8, U$2.D4, U$2.D5, U$2.D7, U$2.D8, U$2.D15, U$2.D16, U$2.D19, U$2.E19, U$2.H9, U$2.H10, U$2.H11, U$2.H12, U$2.H13, U$2.H14, U$2.J8, U$2.J15, U$2.K8, U$2.K15, U$2.L8, U$2.L15, U$2.M8, U$2.M15, U$2.N8, U$2.N15, U$2.P8, U$2.P15, U$2.R9, U$2.R10, U$2.R11, U$2.R12, U$2.R13, U$2.R14, U$2.W4, U$2.W5, U$2.W8, U$2.W15, U$2.W18, U$2.W19, VDD.P$1 (1), VDD_CORE.1
VDD_IO: C2.1 (+), C6.1, JP1.2, U$2.AA2 (Y2), U$2.AA9 (Y9), U$2.AA14 (Y14), U$2.AA21 (Y21), U$2.AB5 (Z5), U$2.AB18 (Z18), U$2.B2, U$2.B9, U$2.B12, U$2.B15, U$2.B20, U$2.B21, U$2.C4, U$2.C6, U$2.C11, U$2.C17, U$2.D20, U$2.E20, U$2.F3, U$2.F20, U$2.G3, U$2.G20, U$2.H4, U$2.H19, U$2.K2, U$2.K21, U$2.N2, U$2.N21, U$2.R4, U$2.R19, U$2.R20, U$2.T4, U$2.U3, U$2.U20, U$2.U21, U$2.V1, U$2.V21, U$2.V22, U$2.Y6 (X6), U$2.Y16 (X16), U$2.Y17 (X17), U$4.P$1 (1), VDD_IO.1
VREF: J1.H1

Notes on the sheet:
Power
FMC Connector
*FMC board to board connector labeled with the pins from the Trenz Electronic TEBF0808 connector board.
BGA socket based on the BGA352 socket from UCSD. Some of the pins in the design are intentionally not connected to the socket but allowed for easier schematic layout. There are two power rings, one for the core voltage (0.8V) and one for IO (1.8V).
*1.2V and 1.5V input from bench power supply Supplementary power from FMC is not used to prevent burning out the carrier card.
Test

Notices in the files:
parts and their libraries:
microbuilder: This work is placed in the public domain, and may be freely used for commercial and non-commercial work with the following conditions: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
